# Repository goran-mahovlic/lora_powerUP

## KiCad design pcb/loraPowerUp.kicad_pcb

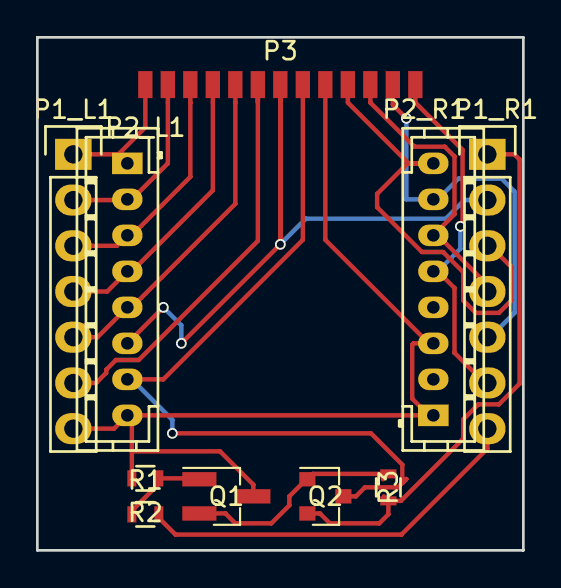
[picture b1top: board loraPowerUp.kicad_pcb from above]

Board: 2 copper layers, 27.0 x 28.5 mm, 10 parts (0 on the bottom side), 17 nets.

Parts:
P1_L1: IN_LEFT; Socket_Strip_Straight_1x07
P1_R1: IN_RIGHT; Socket_Strip_Straight_1x07
P2_L1: DORGI_L; JST_PH_B8B-PH-K_08x2.00mm_Straight
P2_R1: DORGI_R; JST_PH_B8B-PH-K_08x2.00mm_Straight
P3: LORA; lora
Q1: Q_NPN_BCE; SOT-23_Handsoldering
Q2: IRF9540N; SOT-23
R1, R2, R3: 10K; R_0603

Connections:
DIO0: P1_L1.2, P2_L1.2, P3.2
DIO1: P1_L1.3, P2_L1.3, P3.3
DIO2: P1_L1.4, P2_L1.4, P3.4
DIO3: P1_L1.5, P2_L1.5, P3.5
DIO4: P1_L1.6, P3.6
DIO5: P1_R1.2, P2_L1.6, P3.7
GND: P1_L1.7, P2_L1.8, P2_R1.1, P2_R1.3, P3.9, Q1.3, R2.2
LoRaVCC: P2_L1.7, P3.8, Q2.3
MISO: P1_R1.5, P2_R1.7, P3.12
MOSI: P1_R1.4, P2_R1.6, P3.11
NRST: P1_L1.1, P2_L1.1, P3.1
NSS: P1_R1.6, P2_R1.5, P3.13
unnamed: Q1.1, R1.1, R2.1
unnamed: Q1.2, Q2.1, R3.2
ON/OFF: P1_R1.7, R1.2
SCK: P1_R1.3, P2_R1.8, P3.10
VCC: P1_R1.1, Q2.2, R3.1

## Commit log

2018-04-28 Initial add
2018-04-28 Fixing VCC
